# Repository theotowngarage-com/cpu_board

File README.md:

# cpu_board
proto-cpu project based on a 12bit architecture.

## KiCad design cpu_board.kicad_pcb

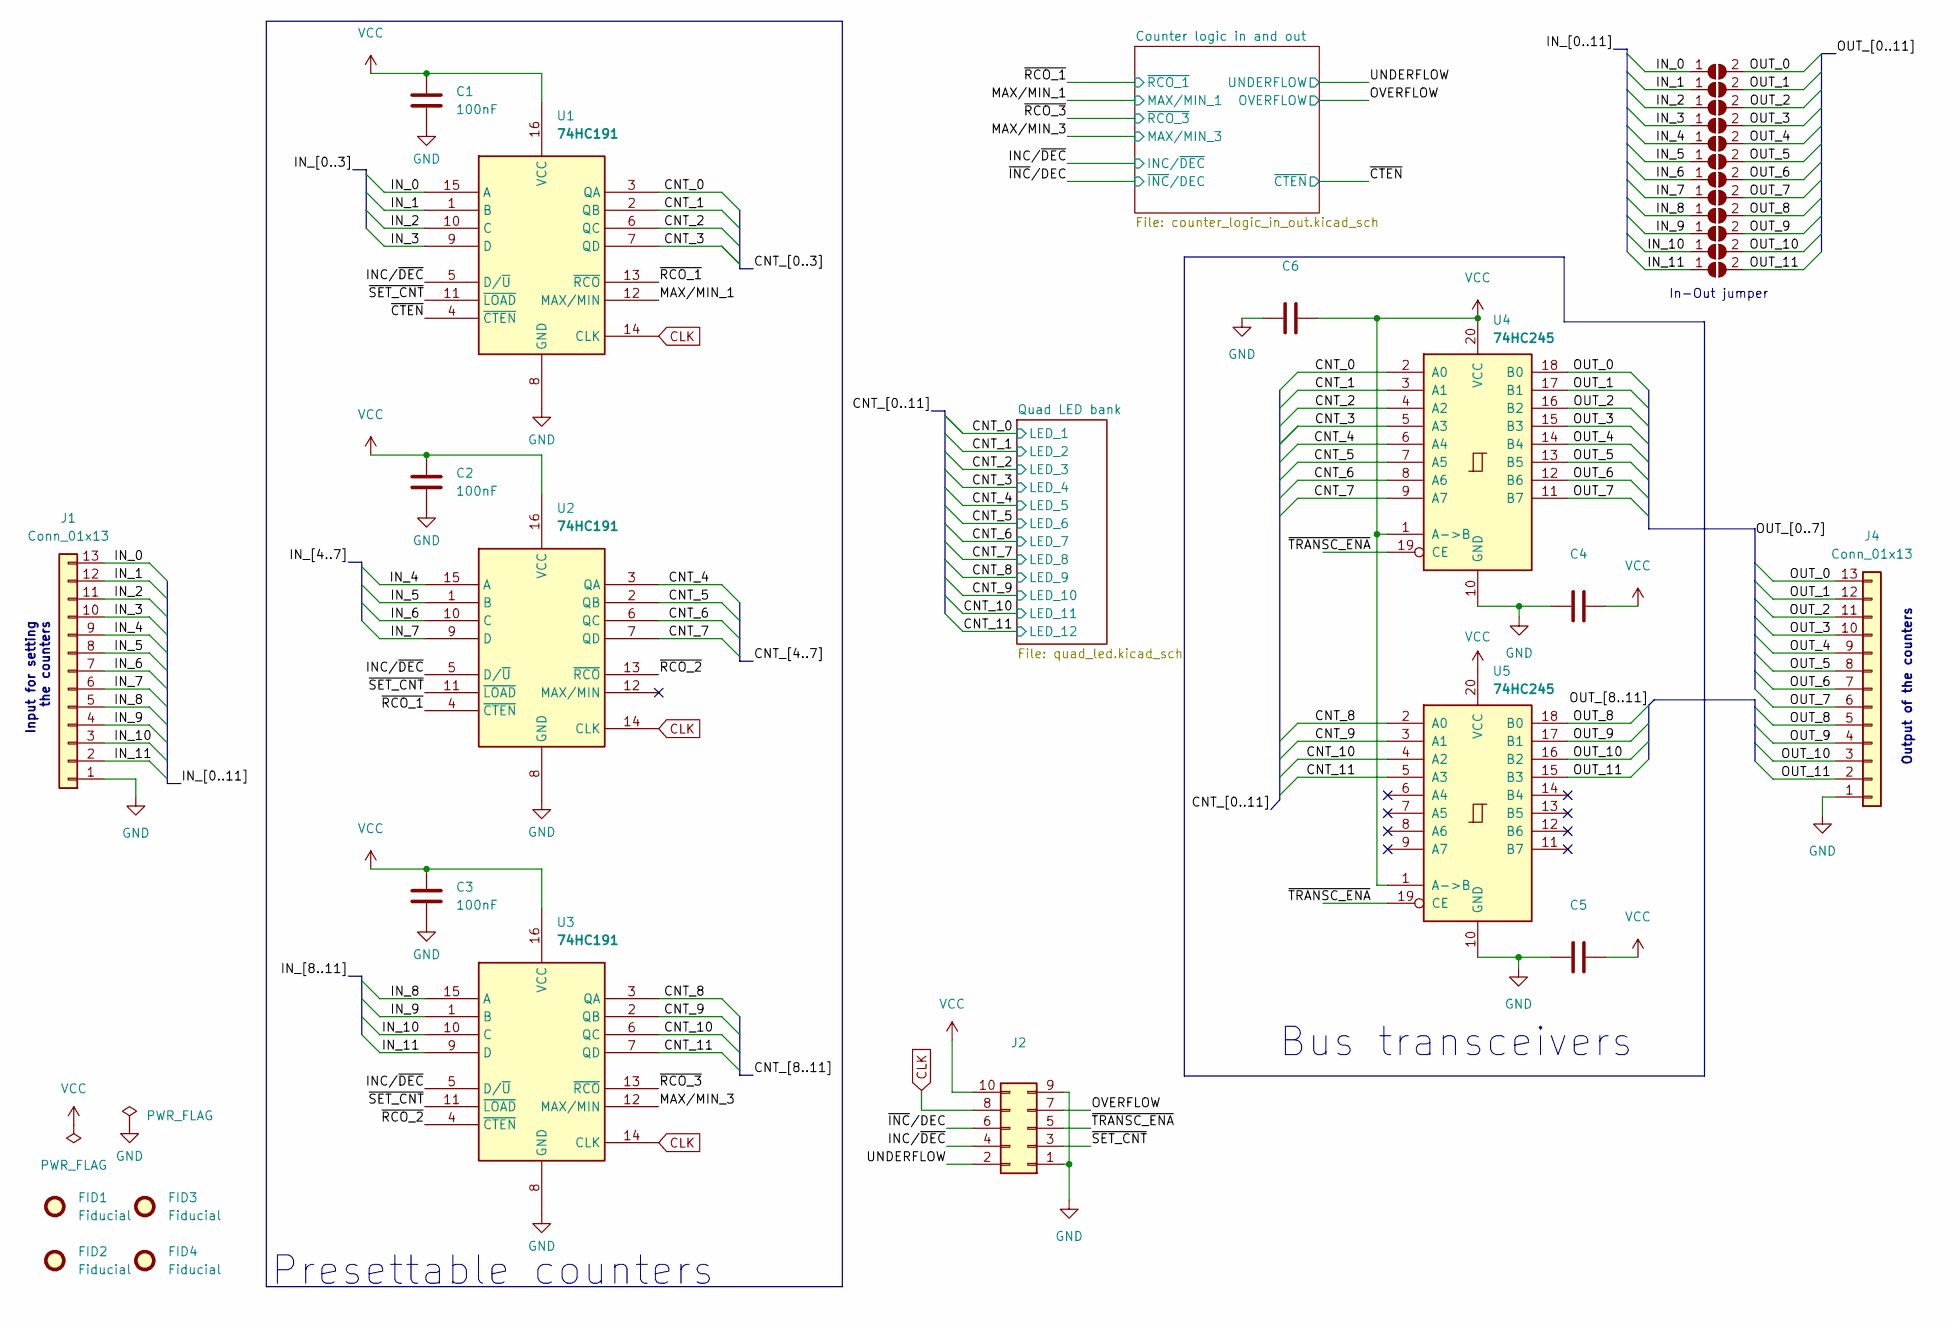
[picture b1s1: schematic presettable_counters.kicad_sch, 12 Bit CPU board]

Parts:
C1, C2, C3: 100nF; C_0603_1608Metric_Pad1.08x0.95mm_HandSolder
C4, C5, C6: C_0603_1608Metric_Pad1.08x0.95mm_HandSolder
FID1, FID2, FID3, FID4: Fiducial; Fiducial_1.5mm_Mask3mm
J1, J4: Conn_01x13; PinHeader_1x13_P2.54mm_Vertical
J2: Conn_02x05_Odd_Even; PinHeader_2x05_P2.54mm_Vertical
J3, J5, J6, J7, J8, J9, J10, J11, J12, J13, J14, J15: Conn_02x12_Odd_Even; SolderJumper-2_P1.3mm_Open_RoundedPad1.0x1.5mm
U1, U2, U3: 74HC191; SOIC-16_3.9x9.9mm_P1.27mm
U4, U5: 74HC245; SOIC-20W_7.5x12.8mm_P1.27mm

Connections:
/Presettable counters/CNT_0: U1.3 (QA), U4.2 (A0); also elsewhere on the board
/Presettable counters/CNT_1: U1.2 (QB), U4.3 (A1); also elsewhere on the board
/Presettable counters/CNT_2: U1.6 (QC), U4.4 (A2); also elsewhere on the board
/Presettable counters/CNT_3: U1.7 (QD), U4.5 (A3); also elsewhere on the board
/Presettable counters/CNT_4: U2.3 (QA), U4.6 (A4); also elsewhere on the board
/Presettable counters/CNT_5: U2.2 (QB), U4.7 (A5); also elsewhere on the board
/Presettable counters/CNT_6: U2.6 (QC), U4.8 (A6); also elsewhere on the board
/Presettable counters/CNT_7: U2.7 (QD), U4.9 (A7); also elsewhere on the board
/Presettable counters/CNT_8: U3.3 (QA), U5.2 (A0); also elsewhere on the board
/Presettable counters/CNT_9: U3.2 (QB), U5.3 (A1); also elsewhere on the board
/Presettable counters/CNT_10: U3.6 (QC), U5.4 (A2); also elsewhere on the board
/Presettable counters/CNT_11: U3.7 (QD), U5.5 (A3); also elsewhere on the board
/Presettable counters/INC/~DEC: J2.4, U1.5 (D/~U), U2.5 (D/~U), U3.5 (D/~U); also elsewhere on the board
/Presettable counters/IN_0: J1.13, J3.1 (A), U1.15 (A)
/Presettable counters/IN_1: J1.12, J5.1 (A), U1.1 (B)
/Presettable counters/IN_2: J1.11, J6.1 (A), U1.10 (C)
/Presettable counters/IN_3: J1.10, J7.1 (A), U1.9 (D)
/Presettable counters/IN_4: J1.9, J8.1 (A), U2.15 (A)
/Presettable counters/IN_5: J1.8, J9.1 (A), U2.1 (B)
/Presettable counters/IN_6: J1.7, J10.1 (A), U2.10 (C)
/Presettable counters/IN_7: J1.6, J11.1 (A), U2.9 (D)
/Presettable counters/IN_8: J1.5, J12.1 (A), U3.15 (A)
/Presettable counters/IN_9: J1.4, J13.1 (A), U3.1 (B)
/Presettable counters/IN_10: J1.3, J14.1 (A), U3.10 (C)
/Presettable counters/IN_11: J1.2, J15.1 (A), U3.9 (D)
/Presettable counters/MAX/MIN_1: U1.12 (MAX/MIN); also elsewhere on the board
/Presettable counters/MAX/MIN_3: U3.12 (MAX/MIN); also elsewhere on the board
/Presettable counters/OUT_0: J3.2 (B), J4.13, U4.18 (B0)
/Presettable counters/OUT_1: J4.12, J5.2 (B), U4.17 (B1)
/Presettable counters/OUT_2: J4.11, J6.2 (B), U4.16 (B2)
/Presettable counters/OUT_3: J4.10, J7.2 (B), U4.15 (B3)
/Presettable counters/OUT_4: J4.9, J8.2 (B), U4.14 (B4)
/Presettable counters/OUT_5: J4.8, J9.2 (B), U4.13 (B5)
/Presettable counters/OUT_6: J4.7, J10.2 (B), U4.12 (B6)
/Presettable counters/OUT_7: J4.6, J11.2 (B), U4.11 (B7)
/Presettable counters/OUT_8: J4.5, J12.2 (B), U5.18 (B0)
/Presettable counters/OUT_9: J4.4, J13.2 (B), U5.17 (B1)
/Presettable counters/OUT_10: J4.3, J14.2 (B), U5.16 (B2)
/Presettable counters/OUT_11: J4.2, J15.2 (B), U5.15 (B3)
/Presettable counters/OVERFLOW: J2.7; also elsewhere on the board
/Presettable counters/UNDERFLOW: J2.2; also elsewhere on the board
/Presettable counters/~CTEN: U1.4 (~CTEN); also elsewhere on the board
/Presettable counters/~INC/DEC: J2.6; also elsewhere on the board
/Presettable counters/~RCO_1: U1.13 (~RCO), U2.4 (~CTEN); also elsewhere on the board
/Presettable counters/~RCO_2: U2.13 (~RCO), U3.4 (~CTEN)
/Presettable counters/~RCO_3: U3.13 (~RCO); also elsewhere on the board
/Presettable counters/~SET_CNT: J2.3, U1.11 (~LOAD), U2.11 (~LOAD), U3.11 (~LOAD)
/Presettable counters/~TRANSC_ENA: J2.5, U4.19 (CE), U5.19 (CE)
CLK: J2.8, U1.14 (CLK), U2.14 (CLK), U3.14 (CLK)
GND: C1.2, C2.2, C3.2, C4.1, C5.1, C6.1, J1.1, J2.1, J2.9, J4.1, U1.8 (GND), U2.8 (GND), U3.8 (GND), U4.10 (GND), U5.10 (GND); also elsewhere on the board
VCC: C1.1, C2.1, C3.1, C4.2, C5.2, C6.2, J2.10, U1.16 (VCC), U2.16 (VCC), U3.16 (VCC), U4.1 (A->B), U4.20 (VCC), U5.1 (A->B), U5.20 (VCC); also elsewhere on the board

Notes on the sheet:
Presettable counters
Output of the counters
In-Out jumper
Input for setting the counters
Bus transceivers

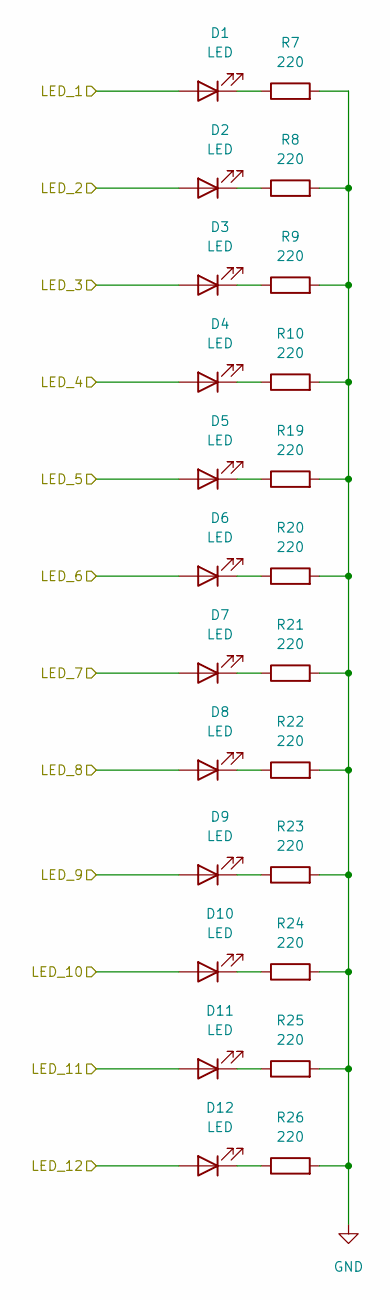
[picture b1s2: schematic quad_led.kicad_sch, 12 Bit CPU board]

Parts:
D1, D2, D3, D4, D5, D6, D7, D8, D9, D10, D11, D12: LED; LED_1206_3216Metric_Pad1.42x1.75mm_HandSolder
R7, R8, R9, R10, R19, R20, R21, R22, R23, R24, R25, R26: 220; R_1206_3216Metric_Pad1.30x1.75mm_HandSolder

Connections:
/Presettable counters/CNT_0: D1.2 (A); also elsewhere on the board
/Presettable counters/CNT_1: D2.2 (A); also elsewhere on the board
/Presettable counters/CNT_2: D3.2 (A); also elsewhere on the board
/Presettable counters/CNT_3: D4.2 (A); also elsewhere on the board
/Presettable counters/CNT_4: D5.2 (A); also elsewhere on the board
/Presettable counters/CNT_5: D6.2 (A); also elsewhere on the board
/Presettable counters/CNT_6: D7.2 (A); also elsewhere on the board
/Presettable counters/CNT_7: D8.2 (A); also elsewhere on the board
/Presettable counters/CNT_8: D9.2 (A); also elsewhere on the board
/Presettable counters/CNT_9: D10.2 (A); also elsewhere on the board
/Presettable counters/CNT_10: D11.2 (A); also elsewhere on the board
/Presettable counters/CNT_11: D12.2 (A); also elsewhere on the board
GND: R7.2, R8.2, R9.2, R10.2, R19.2, R20.2, R21.2, R22.2, R23.2, R24.2, R25.2, R26.2; also elsewhere on the board
unnamed: D1.1 (K), R7.1
unnamed: D2.1 (K), R8.1
unnamed: D3.1 (K), R9.1
unnamed: D4.1 (K), R10.1
unnamed: D5.1 (K), R19.1
unnamed: D6.1 (K), R20.1
unnamed: D7.1 (K), R21.1
unnamed: D8.1 (K), R22.1
unnamed: D9.1 (K), R23.1
unnamed: D10.1 (K), R24.1
unnamed: D11.1 (K), R25.1
unnamed: D12.1 (K), R26.1

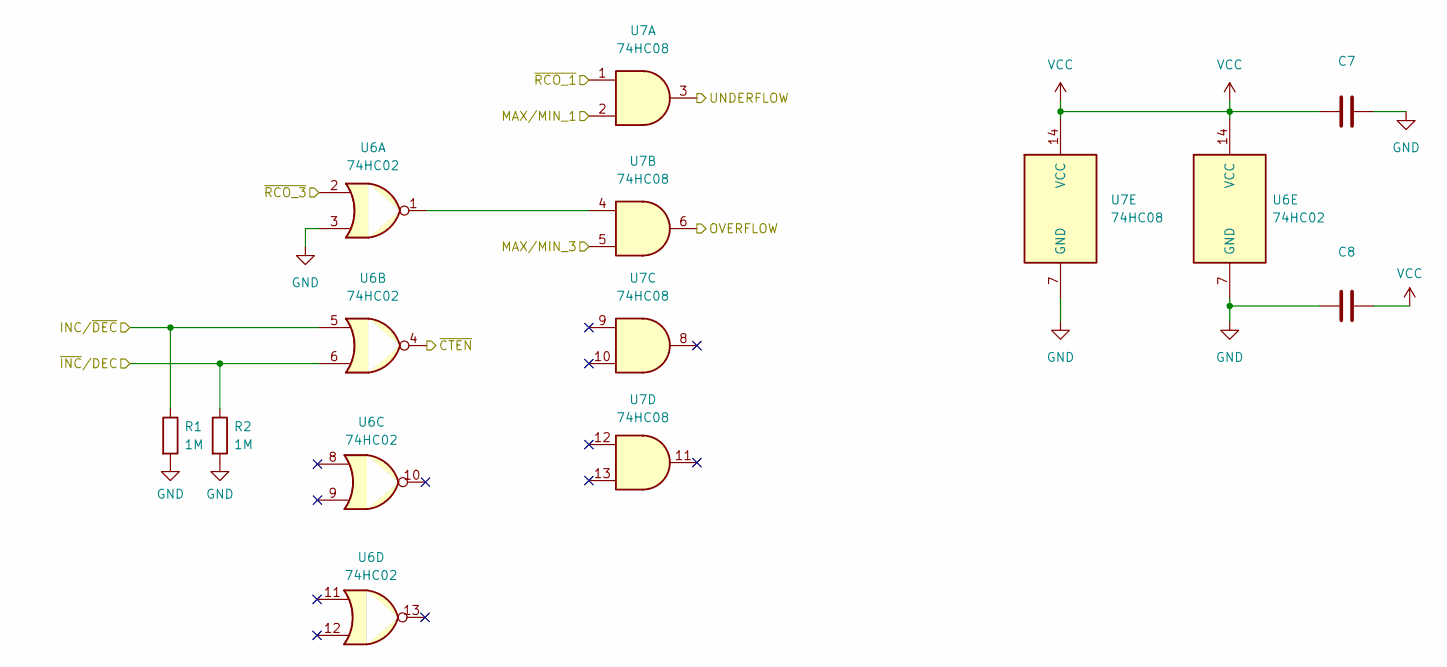
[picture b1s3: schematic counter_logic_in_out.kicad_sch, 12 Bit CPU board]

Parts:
C7, C8: C_0603_1608Metric_Pad1.08x0.95mm_HandSolder
R1, R2: 1M; R_1206_3216Metric_Pad1.30x1.75mm_HandSolder
U6: 74HC02; SOIC-14_3.9x8.7mm_P1.27mm
U7: 74HC08; SOIC-14_3.9x8.7mm_P1.27mm

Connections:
/Presettable counters/INC/~DEC: R1.1, U6.5; also elsewhere on the board
/Presettable counters/MAX/MIN_1: U7.2; also elsewhere on the board
/Presettable counters/MAX/MIN_3: U7.5; also elsewhere on the board
/Presettable counters/OVERFLOW: U7.6; also elsewhere on the board
/Presettable counters/UNDERFLOW: U7.3; also elsewhere on the board
/Presettable counters/~CTEN: U6.4; also elsewhere on the board
/Presettable counters/~INC/DEC: R2.1, U6.6; also elsewhere on the board
/Presettable counters/~RCO_1: U7.1; also elsewhere on the board
/Presettable counters/~RCO_3: U6.2; also elsewhere on the board
GND: C7.2, C8.1, R1.2, R2.2, U6.3, U6.7 (GND), U7.7 (GND); also elsewhere on the board
unnamed: U6.1, U7.4
VCC: C7.1, C8.2, U6.14 (VCC), U7.14 (VCC); also elsewhere on the board

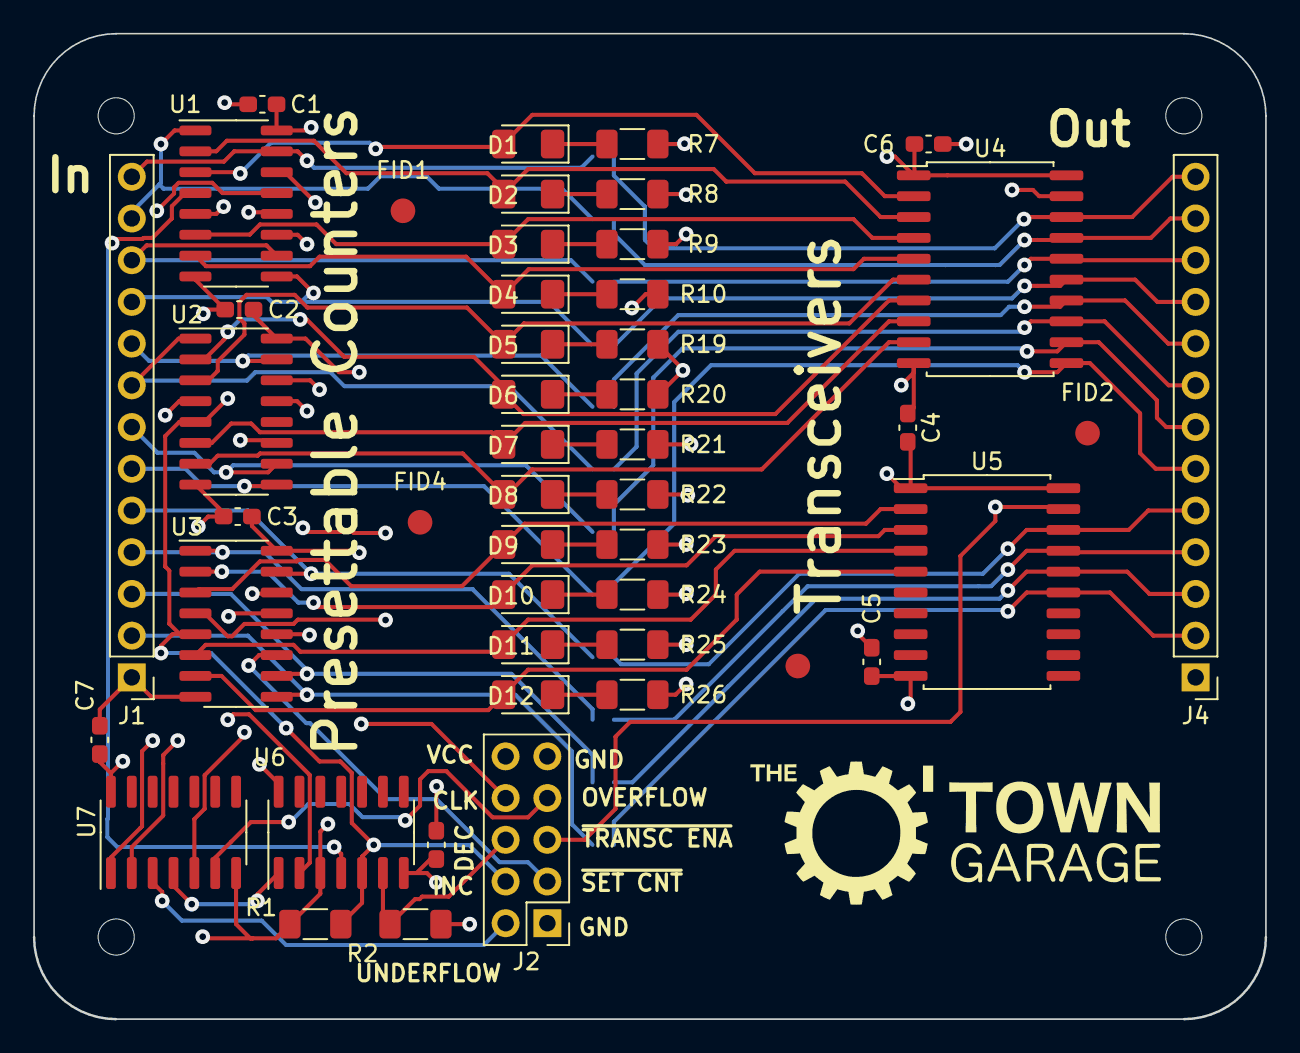
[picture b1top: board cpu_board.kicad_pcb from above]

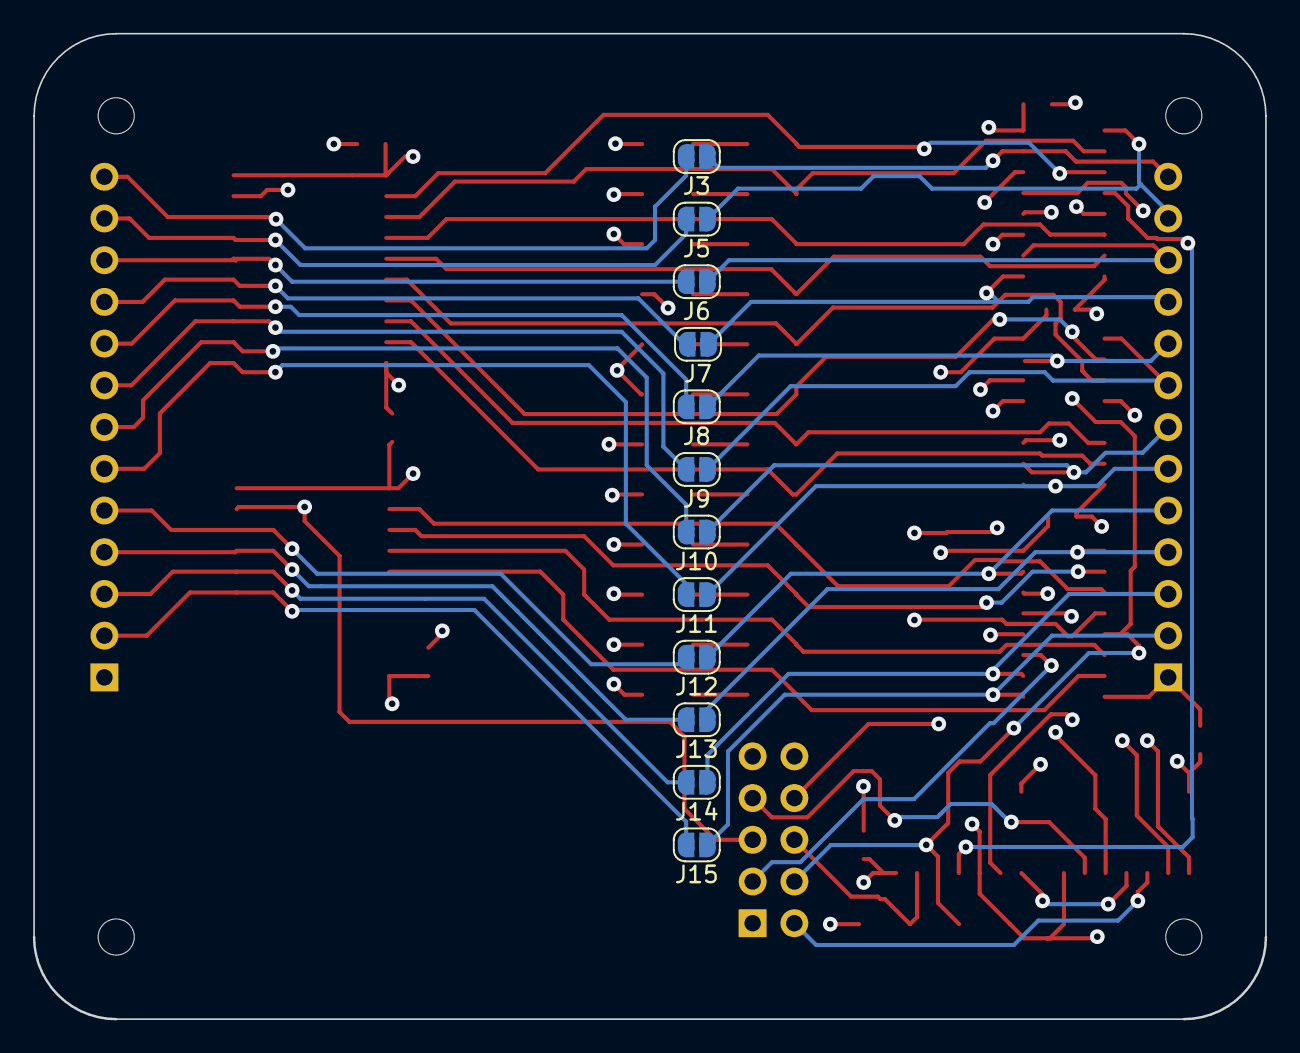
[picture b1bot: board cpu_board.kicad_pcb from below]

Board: 4 copper layers, 75.0 x 60.0 mm, 60 parts (12 on the bottom side), 64 nets.

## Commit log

2023-04-16 Create barebone KiCAD Project.
2023-04-29 Presettable Counter: Electrical diagram
2023-04-29 Review fixes
    - swapped to HC components
    - removed ctn_enable
    - all 12 LEDs merged into 1 sheet
    - No more error with the electrical checker
    - various style improvements
    - Introduce sleep deprivation errors like calling tranceivers d flip flops
2023-04-30 Add gitignore
2023-05-01 Trace the layout
    - Place components on PCB
    - Add silkscreeen
    - Add traces
2023-05-01 Add edge cuts
2023-05-10 routed and pretty
2023-05-10 Updated DRC
2023-05-10 Fixed DRC errors
